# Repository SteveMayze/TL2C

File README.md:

# TL2C - Timed LED Lighting Control

## Introduction
This project is a I2C device to control up to three High Power LED drivers using three PIR13 motion controllers.

The LED drivers in question are already provided on my site and are the SLV 464110 10W 3-36V \(EAN: 4024163087155) constant current High Power LED drivers - as are the motion detectors [PIR13](http://www.elv.de/bewegungsmeldermodul-pir-13.html) modules from [ELV](http://www.elv.de).

The device will be designed around the ATTINY20-SSU micro-controller. The requirements being SPI for In System Programming, I2C to connect to the master device and GPIO for the three High Power LED drivers and the three PIR13 sensors.

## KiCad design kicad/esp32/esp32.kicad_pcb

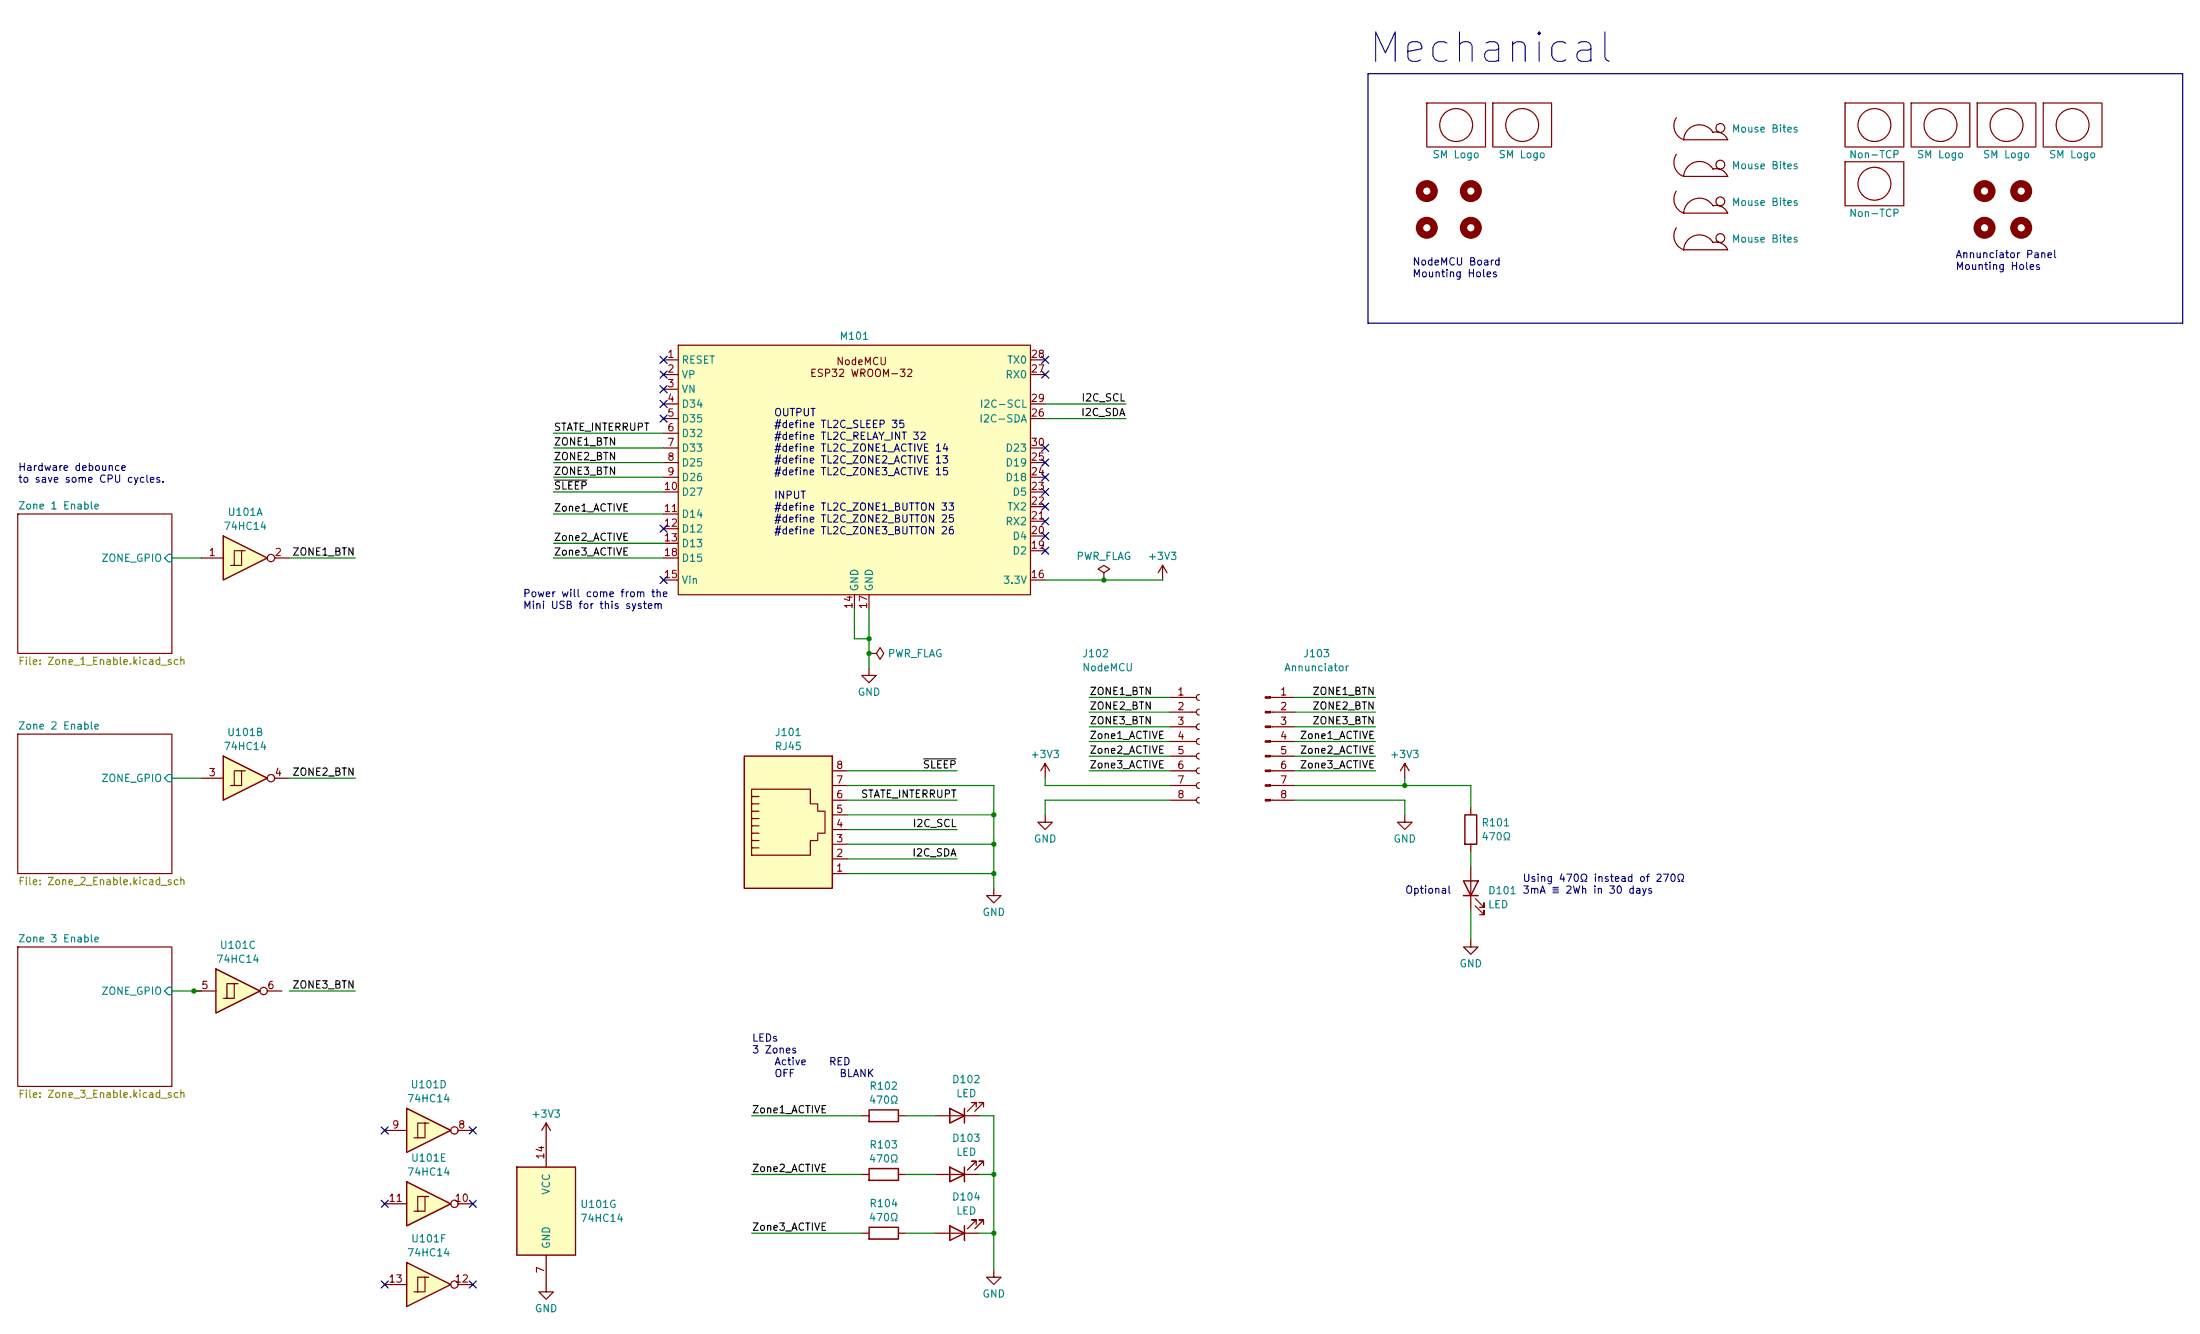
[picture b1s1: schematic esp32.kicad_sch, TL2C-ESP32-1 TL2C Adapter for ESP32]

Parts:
D101, D102, D103, D104: LED; LED_0805_2012Metric
H101, H102, H103, H104: MountingHole; MountingHole_2.1mm
H105, H106, H107, H108: Annunciator MountingHole; MountingHole_2.7mm_M2.5
J101: RJ45; RJ45_8P8C
J102: NodeMCU; PinSocket_1x08_P2.54mm_Vertical
J103: Annunciator; PinHeader_1x08_P2.54mm_Vertical
Lg101, Lg102, Lg106, Lg107: SM Logo; MyBasic_rounded_50_1
Lg103: SM Logo; MyBasic_rounded_50_1_USER5
Lg104, Lg105: Non-TCP; Non_TCP
M101: NodeMCU-ESP32
R101: 470Ω; R_0805_2012Metric
R102, R103, R104: 470Ω; R_Axial_DIN0207_L6.3mm_D2.5mm_P5.08mm_Vertical
U101: 74HC14; SO-14_5.3x10.2mm_P1.27mm
X101, X102, X103, X104: Mouse Bites; MouseBites

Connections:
+3V3: J102.7, J103.7, M101.16 (3.3V), R101.1, U101.14 (VCC); also elsewhere on the board
/I2C_SCL: J101.4, M101.29 (I2C-SCL)
/I2C_SDA: J101.2, M101.26 (I2C-SDA)
/STATE_INTERRUPT: J101.6, M101.6 (D32)
/ZONE1_BTN: J102.1, J103.1, M101.7 (D33), U101.2
/ZONE2_BTN: J102.2, J103.2, M101.8 (D25), U101.4
/ZONE3_BTN: J102.3, J103.3, M101.9 (D26)
/Zone1_ACTIVE: J102.4, J103.4, M101.11 (D14), R102.2
/Zone2_ACTIVE: J102.5, J103.5, M101.13 (D13), R103.2
/Zone3_ACTIVE: J102.6, J103.6, M101.18 (D15), R104.2
/Zone 1 Enable/ZONE_GPIO: U101.1; also elsewhere on the board
/Zone 2 Enable/ZONE_GPIO: U101.3; also elsewhere on the board
/Zone 3 Enable/ZONE_GPIO: U101.5; also elsewhere on the board
/~SLEEP: J101.8, M101.10 (D27)
GND: D101.1 (K), D102.1 (K), D103.1 (K), D104.1 (K), J101.1, J101.3, J101.5, J101.7, J102.8, J103.8, M101.14 (GND), M101.17 (GND), U101.7 (GND); also elsewhere on the board
unnamed: D101.2 (A), R101.2
unnamed: D102.2 (A), R102.1
unnamed: D103.2 (A), R103.1
unnamed: D104.2 (A), R104.1

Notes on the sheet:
LEDs 3 Zones Active RED OFF BLANK
Mechanical
OUTPUT #define TL2C_SLEEP 35 #define TL2C_RELAY_INT 32 #define TL2C_ZONE1_ACTIVE 14 #define TL2C_ZONE2_ACTIVE 13 #define TL2C_ZONE3_ACTIVE 15 INPUT #define TL2C_ZONE1_BUTTON 33 #define TL2C_ZONE2_BUTTON 25 #define TL2C_ZONE3_BUTTON 26
Using 470Ω instead of 270Ω 3mA ≣ 2Wh in 30 days
Power will come from the Mini USB for this system
NodeMCU Board Mounting Holes
Hardware debounce to save some CPU cycles.
Optional
Annunciator Panel Mounting Holes

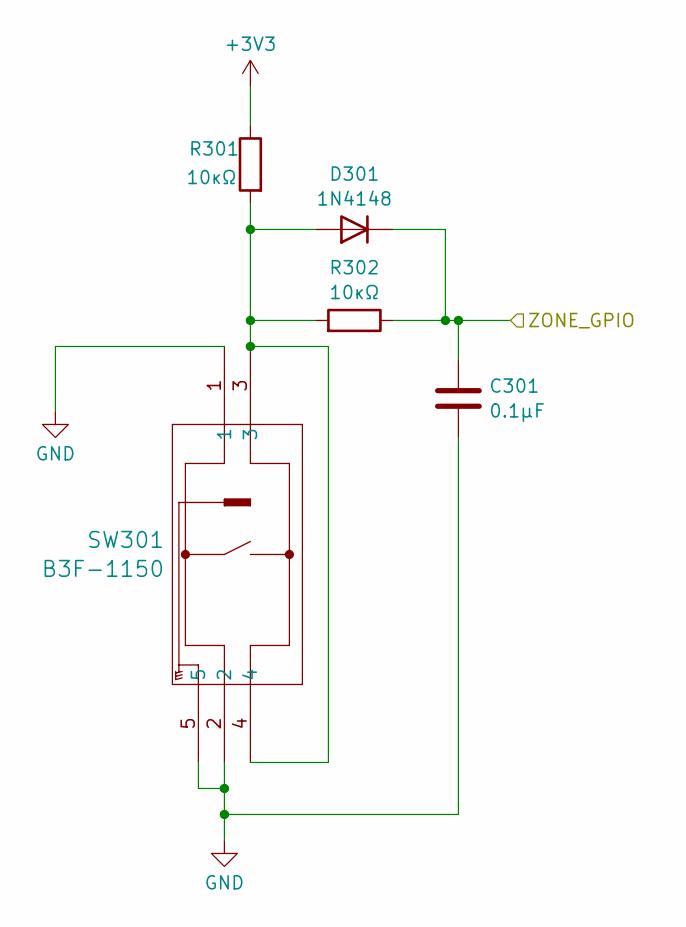
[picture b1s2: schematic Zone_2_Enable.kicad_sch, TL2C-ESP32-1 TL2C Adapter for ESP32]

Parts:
C301: 0.1μF; C_0805_2012Metric
D301: 1N4148; D_SOD-123
R301, R302: 10κΩ; R_0805_2012Metric
SW301: B3F-1150; SW_B3F-1150_OMR

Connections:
+3V3: R301.1; also elsewhere on the board
/Zone 2 Enable/ZONE_GPIO: C301.1, D301.1 (K), R302.1; also elsewhere on the board
GND: C301.2, SW301.1, SW301.2, SW301.5; also elsewhere on the board
unnamed: D301.2 (A), R301.2, R302.2, SW301.3, SW301.4

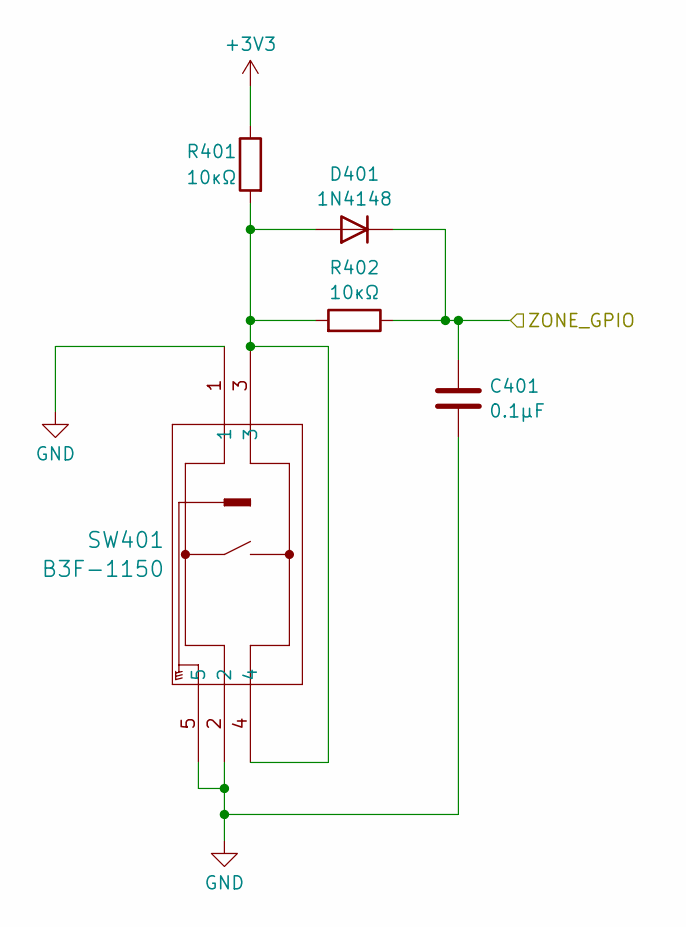
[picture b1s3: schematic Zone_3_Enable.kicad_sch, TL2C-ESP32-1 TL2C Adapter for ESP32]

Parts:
C401: 0.1μF; C_0805_2012Metric
D401: 1N4148; D_SOD-123
R401, R402: 10κΩ; R_0805_2012Metric
SW401: B3F-1150; SW_B3F-1150_OMR

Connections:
+3V3: R401.1; also elsewhere on the board
/Zone 3 Enable/ZONE_GPIO: C401.1, D401.1 (K), R402.1; also elsewhere on the board
GND: C401.2, SW401.1, SW401.2, SW401.5; also elsewhere on the board
unnamed: D401.2 (A), R401.2, R402.2, SW401.3, SW401.4

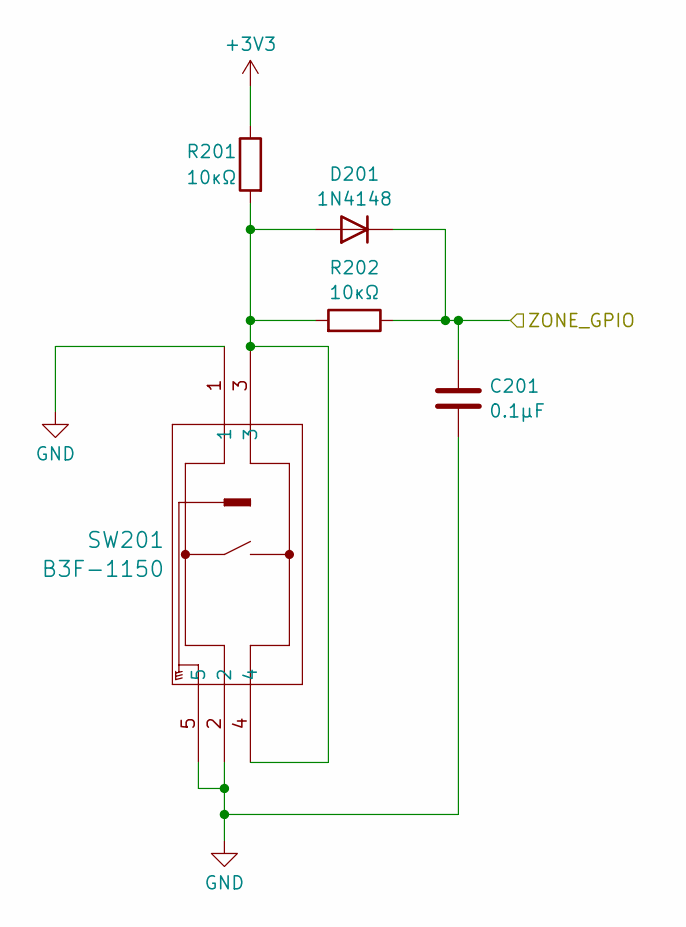
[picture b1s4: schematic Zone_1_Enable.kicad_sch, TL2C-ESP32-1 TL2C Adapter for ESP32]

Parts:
C201: 0.1μF; C_0805_2012Metric
D201: 1N4148; D_SOD-123
R201, R202: 10κΩ; R_0805_2012Metric
SW201: B3F-1150; SW_B3F-1150_OMR

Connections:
+3V3: R201.1; also elsewhere on the board
/Zone 1 Enable/ZONE_GPIO: C201.1, D201.1 (K), R202.1; also elsewhere on the board
GND: C201.2, SW201.1, SW201.2, SW201.5; also elsewhere on the board
unnamed: D201.2 (A), R201.2, R202.2, SW201.3, SW201.4

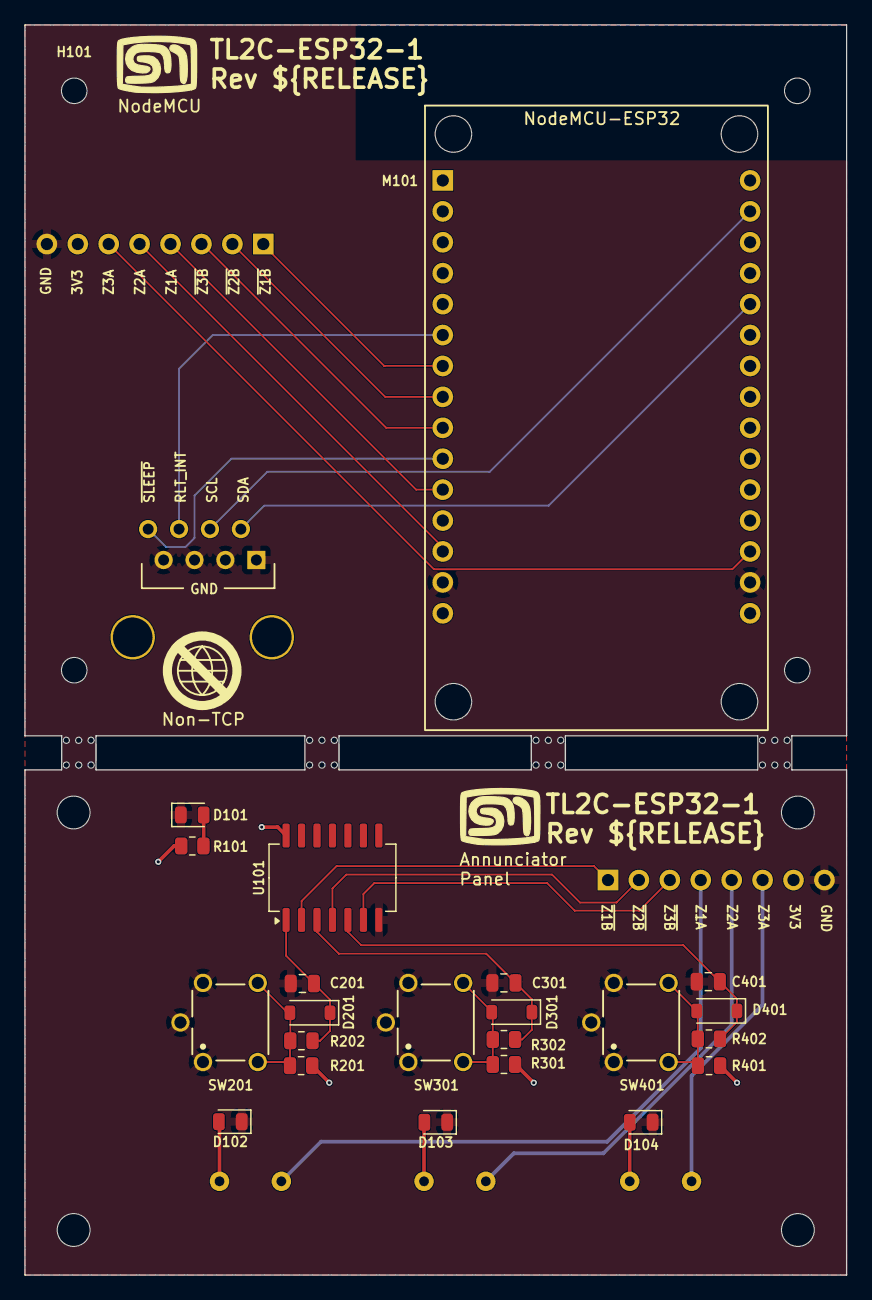
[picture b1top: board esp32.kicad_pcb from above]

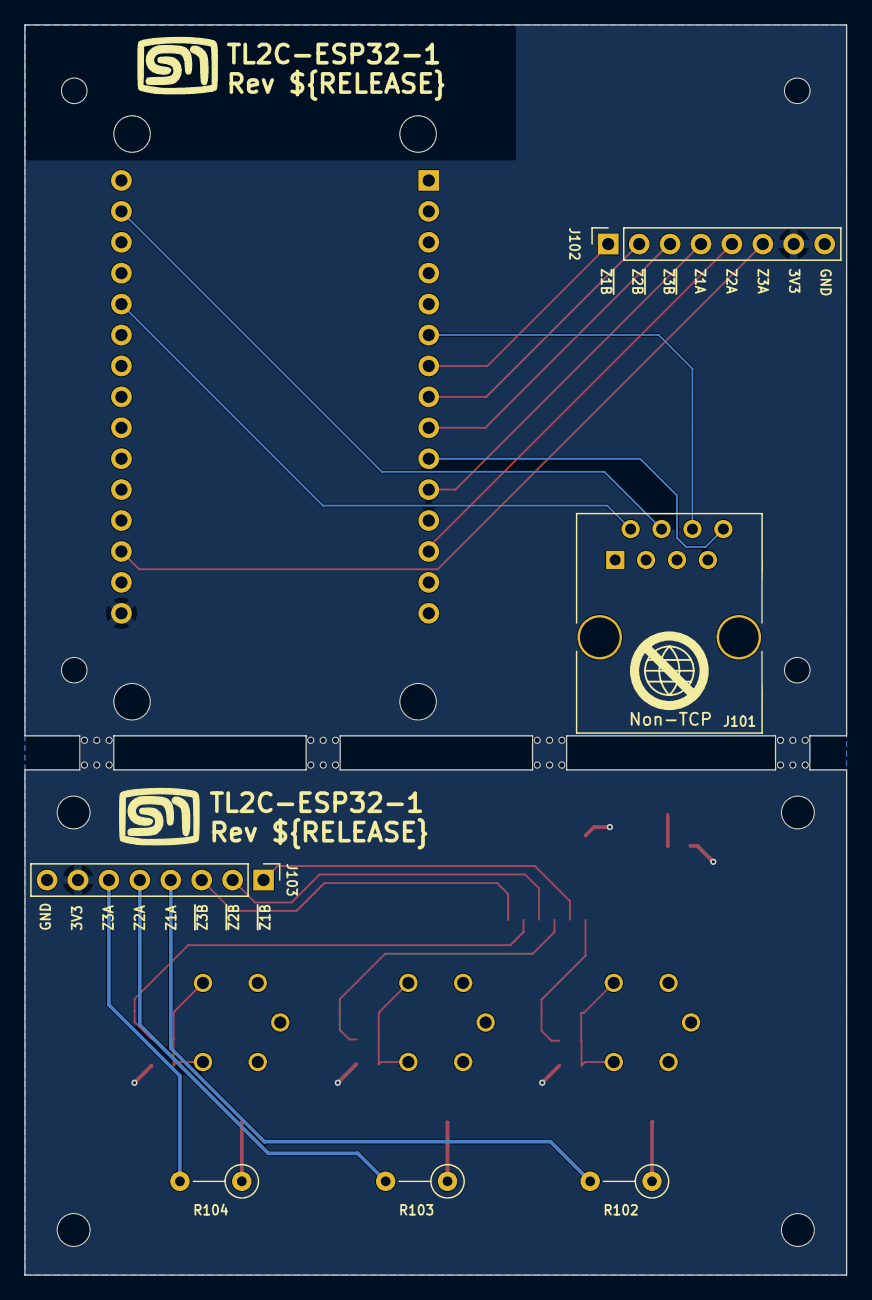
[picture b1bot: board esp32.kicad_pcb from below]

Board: 2 copper layers, 67.5 x 102.7 mm, 47 parts (9 on the bottom side), 22 nets.

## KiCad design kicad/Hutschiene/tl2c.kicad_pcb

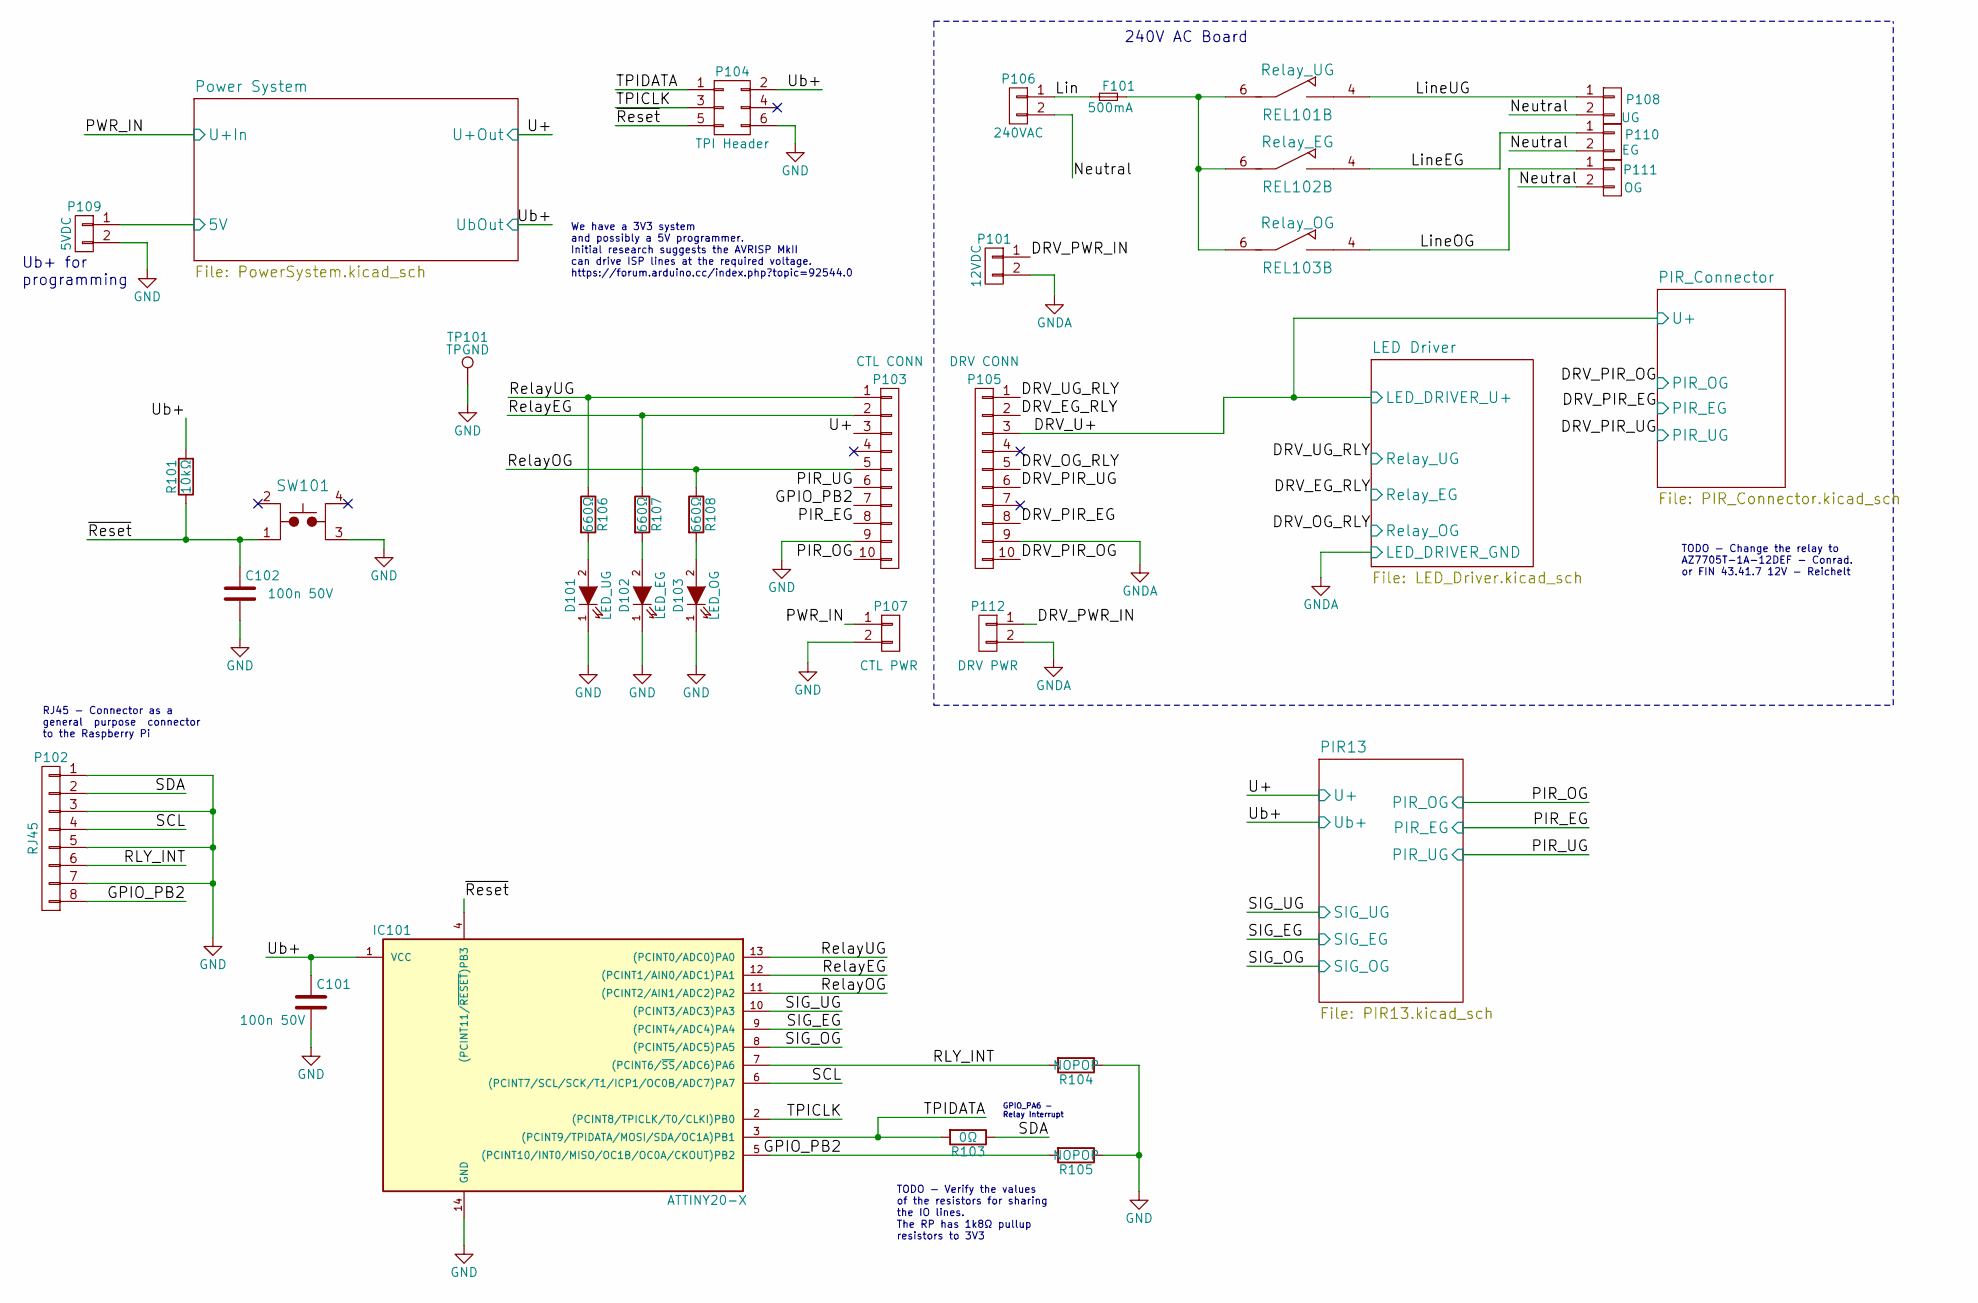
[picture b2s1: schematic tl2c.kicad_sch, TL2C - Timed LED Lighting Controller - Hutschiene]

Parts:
C101, C102: 100n 50V; C_0805
D101: LED_UG; LED_0805_HandSoldering
D102: LED_EG; LED_0805_HandSoldering
D103: LED_OG; LED_0805_HandSoldering
F101: 500mA; Fuse_TE5_Littlefuse-ESKA_887_O14; Digikey-PN Value
IC101: ATTINY20-X; SOIC-14_3.9x8.7mm_Pitch1.27mm; Digikey-PN ATTINY20-SSURCT-ND
P101: 12VDC; PCB_Screw_Terminal_Block_5.08mm_x_2; Digikey-PN Value
P102: RJ45; RJ45_8P8C
P103: CTL CONN; Pin_Header_Straight_2x05_Pitch2.54mm
P104: TPI Header; Tag-Connect_TC2030-IDC-NL; Digikey-PN Value
P105: DRV CONN; Socket_Strip_Straight_2x05_Pitch2.54mm
P106: 240VAC; PCB_Screw_Terminal_Block_5.08mm_x_2; Digikey-PN Value
P107: CTL PWR; Pin_Header_Straight_1x02_Pitch2.54mm
P108: UG; PCB_Screw_Terminal_Block_5.08mm_x_2; Digikey-PN Value
P109: 5VDC; Pin_Header_Straight_1x02_Pitch2.54mm; Digikey-PN Value
P110: EG; PCB_Screw_Terminal_Block_5.08mm_x_2; Digikey-PN Value
P111: OG; PCB_Screw_Terminal_Block_5.08mm_x_2; Digikey-PN Value
P112: DRV PWR; Pin_Header_Straight_1x02_Pitch2.54mm
R101: 10kΩ; R_0805
R103: 0Ω; R_0805
R104, R105: NOPOP; R_0805
R106, R107, R108: 660Ω; R_0805_HandSoldering
REL101: Relay_UG; JW1AFSN-12-F; Digikey-PN Value
REL102: Relay_EG; JW1AFSN-12-F; Digikey-PN Value
REL103: Relay_OG; JW1AFSN-12-F; Digikey-PN Value
SW101: TL3315NF160Q; TACTILE_FSM2JSMAA; Digikey-PN Value
TP101: TPGND; Measurement_Point_Round-SMD-Pad_Small

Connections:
/DRV_PWR_IN: P101.1, P112.1
/GPIO_PB2: IC101.5 ((PCINT10/INT0/MISO/OC1B/OC0A/CKOUT)PB2), P102.8, P103.7, R105.2
/LED Driver/LED_DRIVER_U+: P105.3; also elsewhere on the board
/LED Driver/Relay_EG: P105.2; also elsewhere on the board
/LED Driver/Relay_OG: P105.5; also elsewhere on the board
/LED Driver/Relay_UG: P105.1; also elsewhere on the board
/Lin: F101.1, P106.1
/LineEG: P110.1, REL102.4
/LineOG: P111.1, REL103.4
/LineUG: P108.1, REL101.4
/Neutral: P106.2, P108.2, P110.2, P111.2
/PIR13/PIR_EG: P103.8; also elsewhere on the board
/PIR13/PIR_OG: P103.10; also elsewhere on the board
/PIR13/PIR_UG: P103.6; also elsewhere on the board
/PIR13/SIG_EG: IC101.9 ((PCINT4/ADC4)PA4); also elsewhere on the board
/PIR13/SIG_OG: IC101.8 ((PCINT5/ADC5)PA5); also elsewhere on the board
/PIR13/SIG_UG: IC101.10 ((PCINT3/ADC3)PA3); also elsewhere on the board
/PIR13/U+: P103.3; also elsewhere on the board
/PIR13/Ub+: C101.1, IC101.1 (VCC), P104.2, R101.2; also elsewhere on the board
/PIR_Connector/PIR_EG: P105.8; also elsewhere on the board
/PIR_Connector/PIR_OG: P105.10; also elsewhere on the board
/PIR_Connector/PIR_UG: P105.6; also elsewhere on the board
/Power System/5V: P109.1; also elsewhere on the board
/Power System/U+In: P107.1; also elsewhere on the board
/RLY_INT: IC101.7 ((PCINT6/~SS/ADC6)PA6), P102.6, R104.2
/RelayEG: IC101.12 ((PCINT1/AIN0/ADC1)PA1), P103.2, R107.1
/RelayOG: IC101.11 ((PCINT2/AIN1/ADC2)PA2), P103.5, R108.1
/RelayUG: IC101.13 ((PCINT0/ADC0)PA0), P103.1, R106.1
/SCL: IC101.6 ((PCINT7/SCL/SCK/T1/ICP1/OC0B/ADC7)PA7), P102.4
/SDA: P102.2, R103.1
/TPICLK: IC101.2 ((PCINT8/TPICLK/T0/CLKI)PB0), P104.3
/TPIDATA: IC101.3 ((PCINT9/TPIDATA/MOSI/SDA/OC1A)PB1), P104.1, R103.2
/~Reset: C102.1, IC101.4 ((PCINT11/~RESET)PB3), P104.5, R101.1, SW101.1
GND: C101.2, C102.2, D101.1 (K), D102.1 (K), D103.1 (K), IC101.14 (GND), P102.1, P102.3, P102.5, P102.7, P103.9, P104.6, P107.2, P109.2, R104.1, R105.1, SW101.3, TP101.1; also elsewhere on the board
GNDA: P101.2, P105.9, P112.2; also elsewhere on the board
unnamed: D101.2 (A), R106.2
unnamed: D102.2 (A), R107.2
unnamed: D103.2 (A), R108.2
unnamed: F101.2, REL101.6, REL102.6, REL103.6

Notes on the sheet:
GPIO_PA6 - Relay Interrupt
Ub+ for programming
TODO - Change the relay to AZ7705T-1A-12DEF - Conrad. or FIN 43.41.7 12V - Reichelt
TODO - Verify the values of the resistors for sharing the IO lines.
240V AC Board
RJ45 - Connector as a general purpose connector to the Raspberry Pi
We have a 3V3 system and possibly a 5V programmer. Initial research suggests the AVRISP MkII can drive ISP lines at the required voltage. https://forum.arduino.cc/index.php?topic=92544.0
The RP has 1k8Ω pullup resistors to 3V3

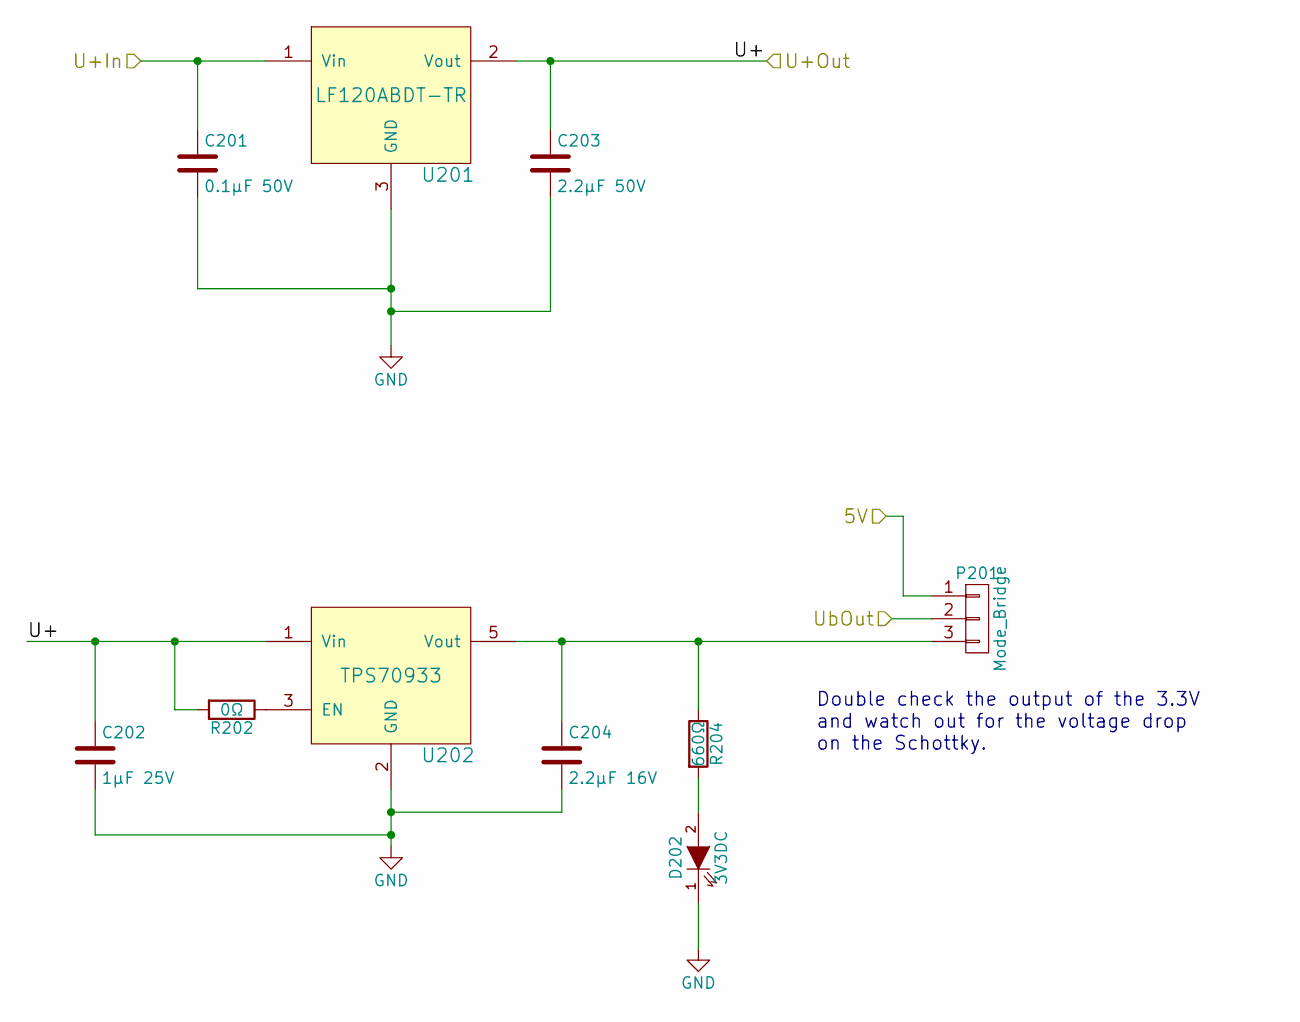
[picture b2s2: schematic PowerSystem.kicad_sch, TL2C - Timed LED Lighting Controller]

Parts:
C201: 0.1μF 50V; C_0805
C202: 1μF 25V; C_0805; Digikey-PN Value
C203: 2.2μF 50V; C_0805; Digikey-PN N/A
C204: 2.2μF 16V; C_0805; Digikey-PN Value
D202: 3V3DC; LED_0805_HandSoldering
P201: Mode_Bridge; Pin_Header_Straight_1x03_Pitch2.54mm
R202: 0Ω; R_0805
R204: 660Ω; R_0805_HandSoldering
U201: LF120ABDT-TR; Digikey-PN 497-8330-1-ND
U202: TPS70933; TPS70933DBVR; Digikey-PN 296-35483-1-ND

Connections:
/PIR13/U+: C202.1, C203.1, R202.2, U201.2 (Vout), U202.1 (Vin); also elsewhere on the board
/PIR13/Ub+: P201.2; also elsewhere on the board
/Power System/5V: P201.1; also elsewhere on the board
/Power System/U+In: C201.1, U201.1 (Vin); also elsewhere on the board
GND: C201.2, C202.2, C203.2, C204.2, D202.1 (K), U201.3 (GND), U202.2 (GND); also elsewhere on the board
unnamed: C204.1, P201.3, R204.1, U202.5 (Vout)
unnamed: D202.2 (A), R204.2
unnamed: R202.1, U202.3 (EN)

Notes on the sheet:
Double check the output of the 3.3V and watch out for the voltage drop on the Schottky.

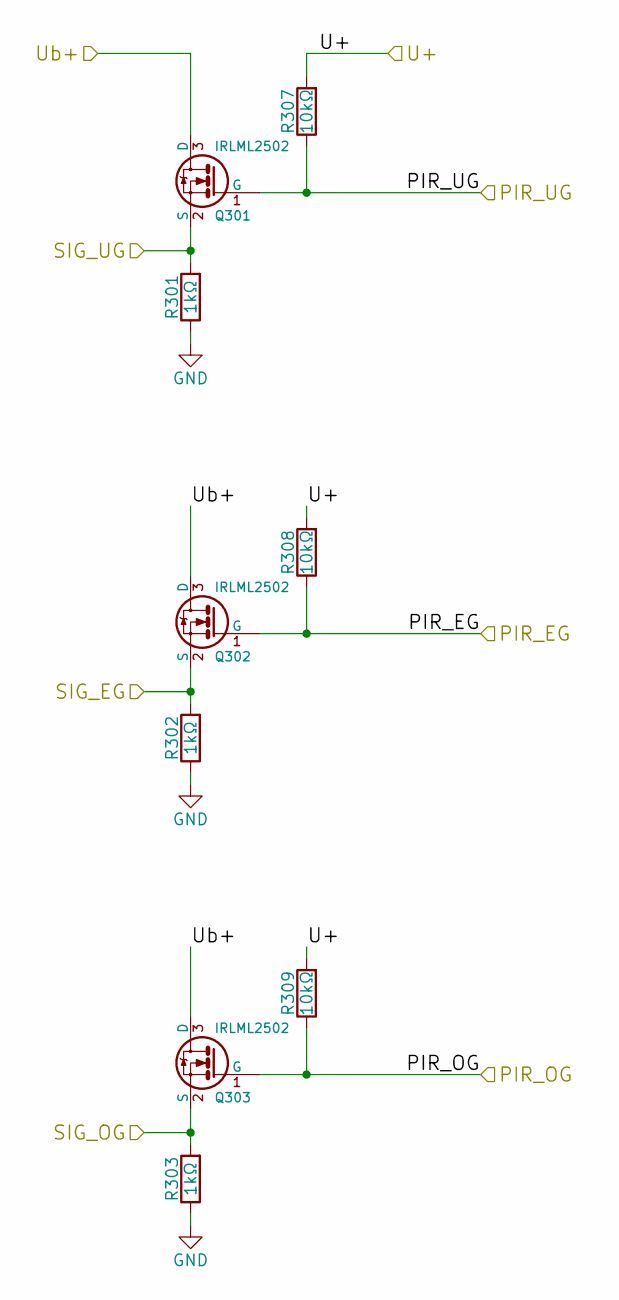
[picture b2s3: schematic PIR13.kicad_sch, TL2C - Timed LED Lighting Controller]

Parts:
Q301, Q302, Q303: IRLML2502; SOT-23; Digikey-PN IRLML2502GTRPBFCT-ND
R301, R302, R303: 1kΩ; R_0805
R307, R308, R309: 10kΩ; R_0805

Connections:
/PIR13/PIR_EG: Q302.1 (G), R308.1; also elsewhere on the board
/PIR13/PIR_OG: Q303.1 (G), R309.1; also elsewhere on the board
/PIR13/PIR_UG: Q301.1 (G), R307.1; also elsewhere on the board
/PIR13/SIG_EG: Q302.2 (S), R302.2; also elsewhere on the board
/PIR13/SIG_OG: Q303.2 (S), R303.2; also elsewhere on the board
/PIR13/SIG_UG: Q301.2 (S), R301.2; also elsewhere on the board
/PIR13/U+: R307.2, R308.2, R309.2; also elsewhere on the board
/PIR13/Ub+: Q301.3 (D), Q302.3 (D), Q303.3 (D); also elsewhere on the board
GND: R301.1, R302.1, R303.1; also elsewhere on the board

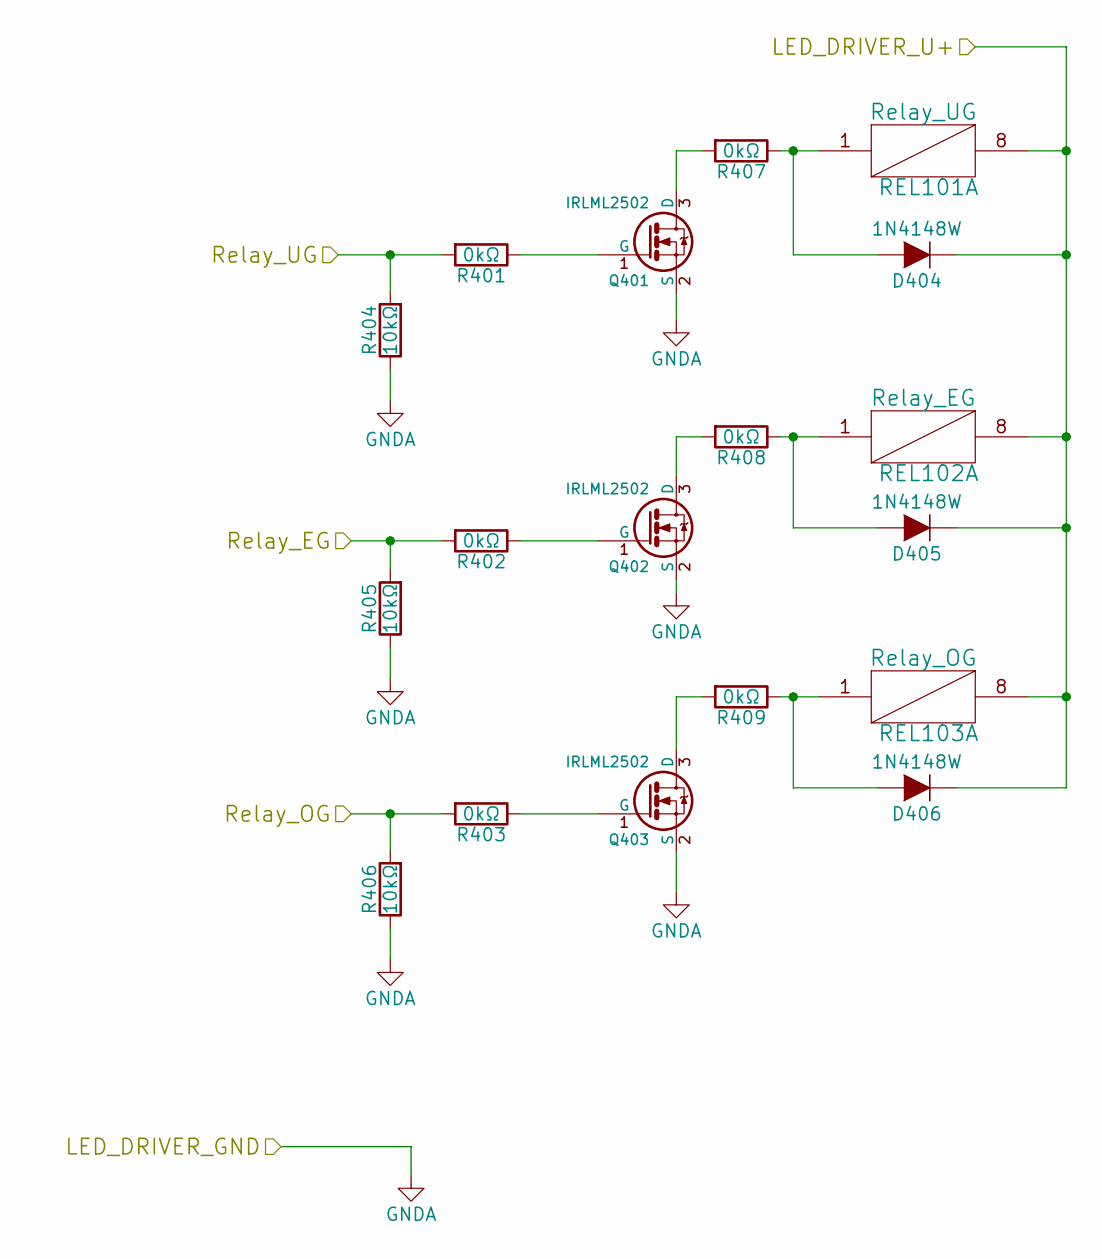
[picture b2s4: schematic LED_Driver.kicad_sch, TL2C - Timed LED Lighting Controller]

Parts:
D404, D405, D406: 1N4148W; SOD-123; Digikey-PN 1N4148W-E3-18CT-ND
Q401: IRLML2502; SOT-23; Digikey-PN IRLML2502GTRPBFCT-ND
Q402, Q403: IRLML2502; SOT-23; Digikey-PN RLML2502GTRPBFCT-ND
R401, R402, R403, R407, R408, R409: 0kΩ; R_0805
R404, R405, R406: 10kΩ; R_0805
REL101: Relay_UG; JW1AFSN-12-F; Digikey-PN N/A
REL102: Relay_EG; JW1AFSN-12-F; Digikey-PN N/A
REL103: Relay_OG; JW1AFSN-12-F; Digikey-PN N/A

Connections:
/LED Driver/LED_DRIVER_U+: D404.1 (K), D405.1 (K), D406.1 (K), REL101.8, REL102.8, REL103.8; also elsewhere on the board
/LED Driver/Relay_EG: R402.2, R405.2; also elsewhere on the board
/LED Driver/Relay_OG: R403.2, R406.2; also elsewhere on the board
/LED Driver/Relay_UG: R401.2, R404.2; also elsewhere on the board
GNDA: Q401.2 (S), Q402.2 (S), Q403.2 (S), R404.1, R405.1, R406.1; also elsewhere on the board
unnamed: D404.2 (A), R407.1, REL101.1
unnamed: D405.2 (A), R408.1, REL102.1
unnamed: D406.2 (A), R409.1, REL103.1
unnamed: Q401.1 (G), R401.1
unnamed: Q401.3 (D), R407.2
unnamed: Q402.1 (G), R402.1
unnamed: Q402.3 (D), R408.2
unnamed: Q403.1 (G), R403.1
unnamed: Q403.3 (D), R409.2

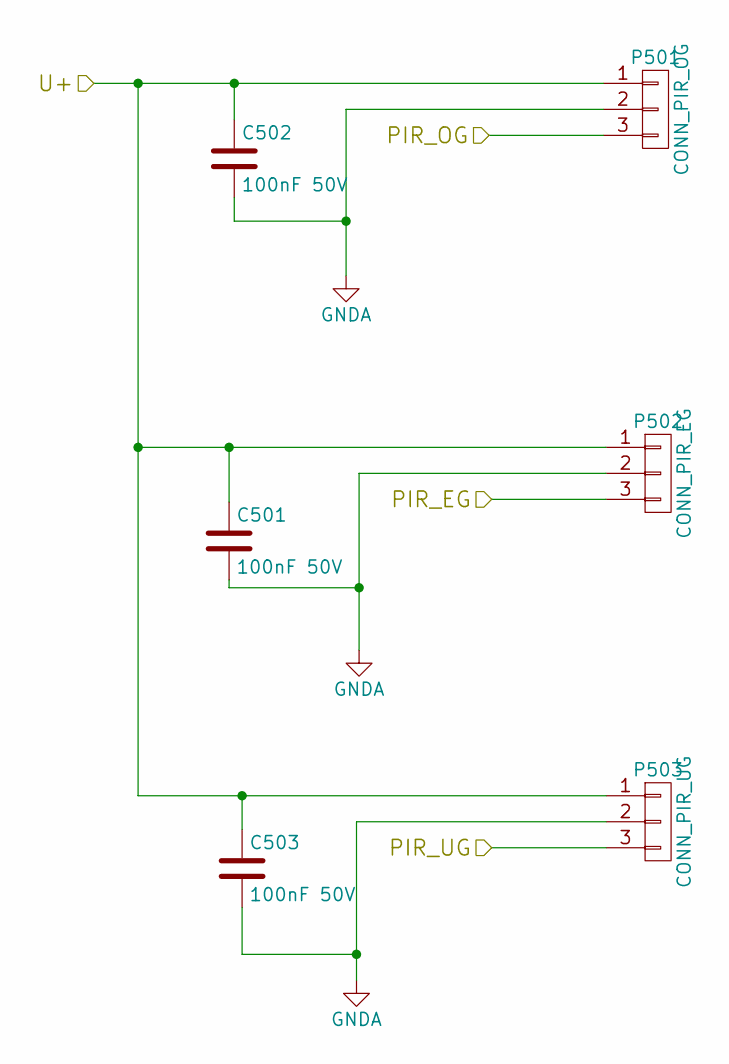
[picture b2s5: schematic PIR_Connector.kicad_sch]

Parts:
C501, C502, C503: 100nF 50V; C_0805_HandSoldering; MPN Value
P501: CONN_PIR_OG; PCB_Screw_Terminal_Block_5.8mm_x_3
P502: CONN_PIR_EG; PCB_Screw_Terminal_Block_5.8mm_x_3
P503: CONN_PIR_UG; PCB_Screw_Terminal_Block_5.8mm_x_3

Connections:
/LED Driver/LED_DRIVER_U+: C501.1, C502.1, C503.1, P501.1, P502.1, P503.1; also elsewhere on the board
/PIR_Connector/PIR_EG: P502.3; also elsewhere on the board
/PIR_Connector/PIR_OG: P501.3; also elsewhere on the board
/PIR_Connector/PIR_UG: P503.3; also elsewhere on the board
GNDA: C501.2, C502.2, C503.2, P501.2, P502.2, P503.2; also elsewhere on the board

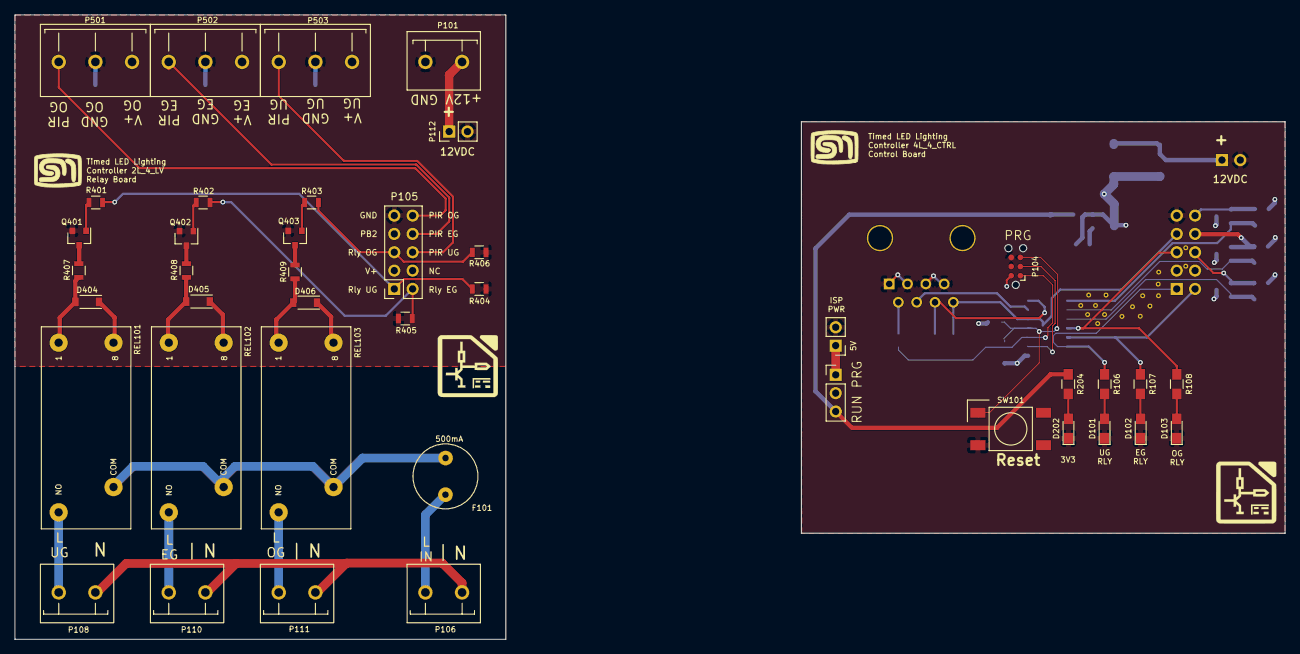
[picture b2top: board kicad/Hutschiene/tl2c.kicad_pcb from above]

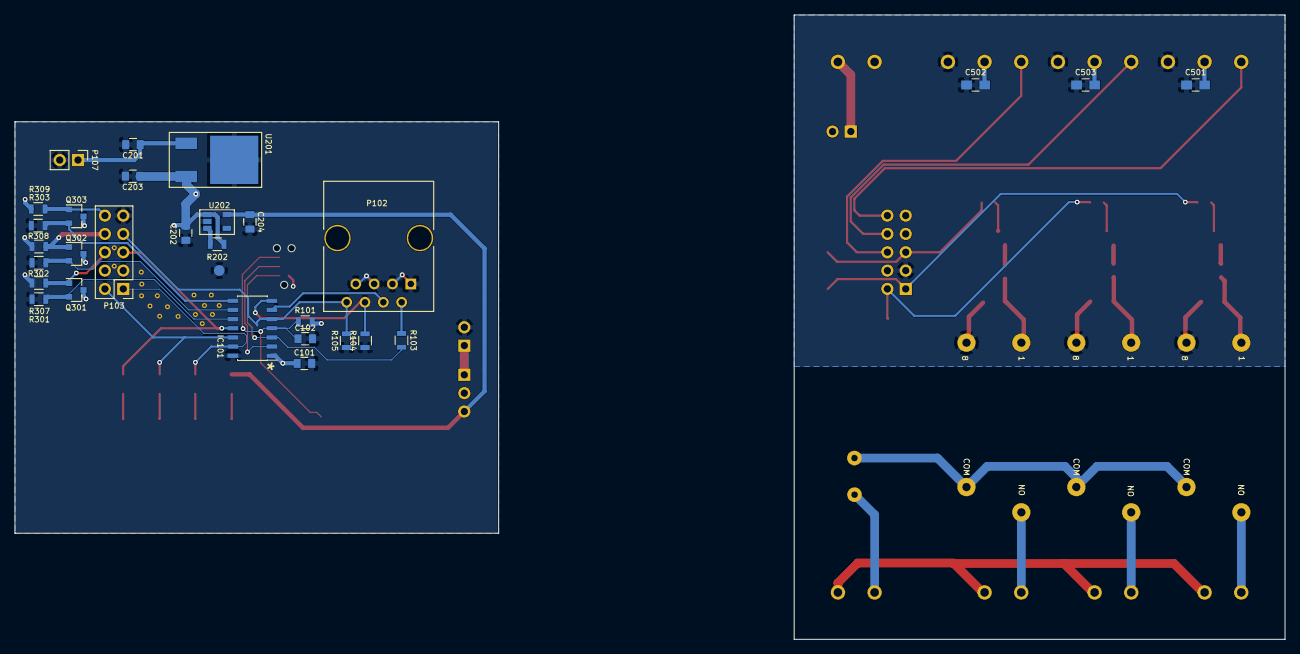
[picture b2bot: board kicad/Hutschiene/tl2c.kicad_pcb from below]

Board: 4 copper layers, 175.9 x 86.5 mm, 71 parts (30 on the bottom side), 51 nets.
